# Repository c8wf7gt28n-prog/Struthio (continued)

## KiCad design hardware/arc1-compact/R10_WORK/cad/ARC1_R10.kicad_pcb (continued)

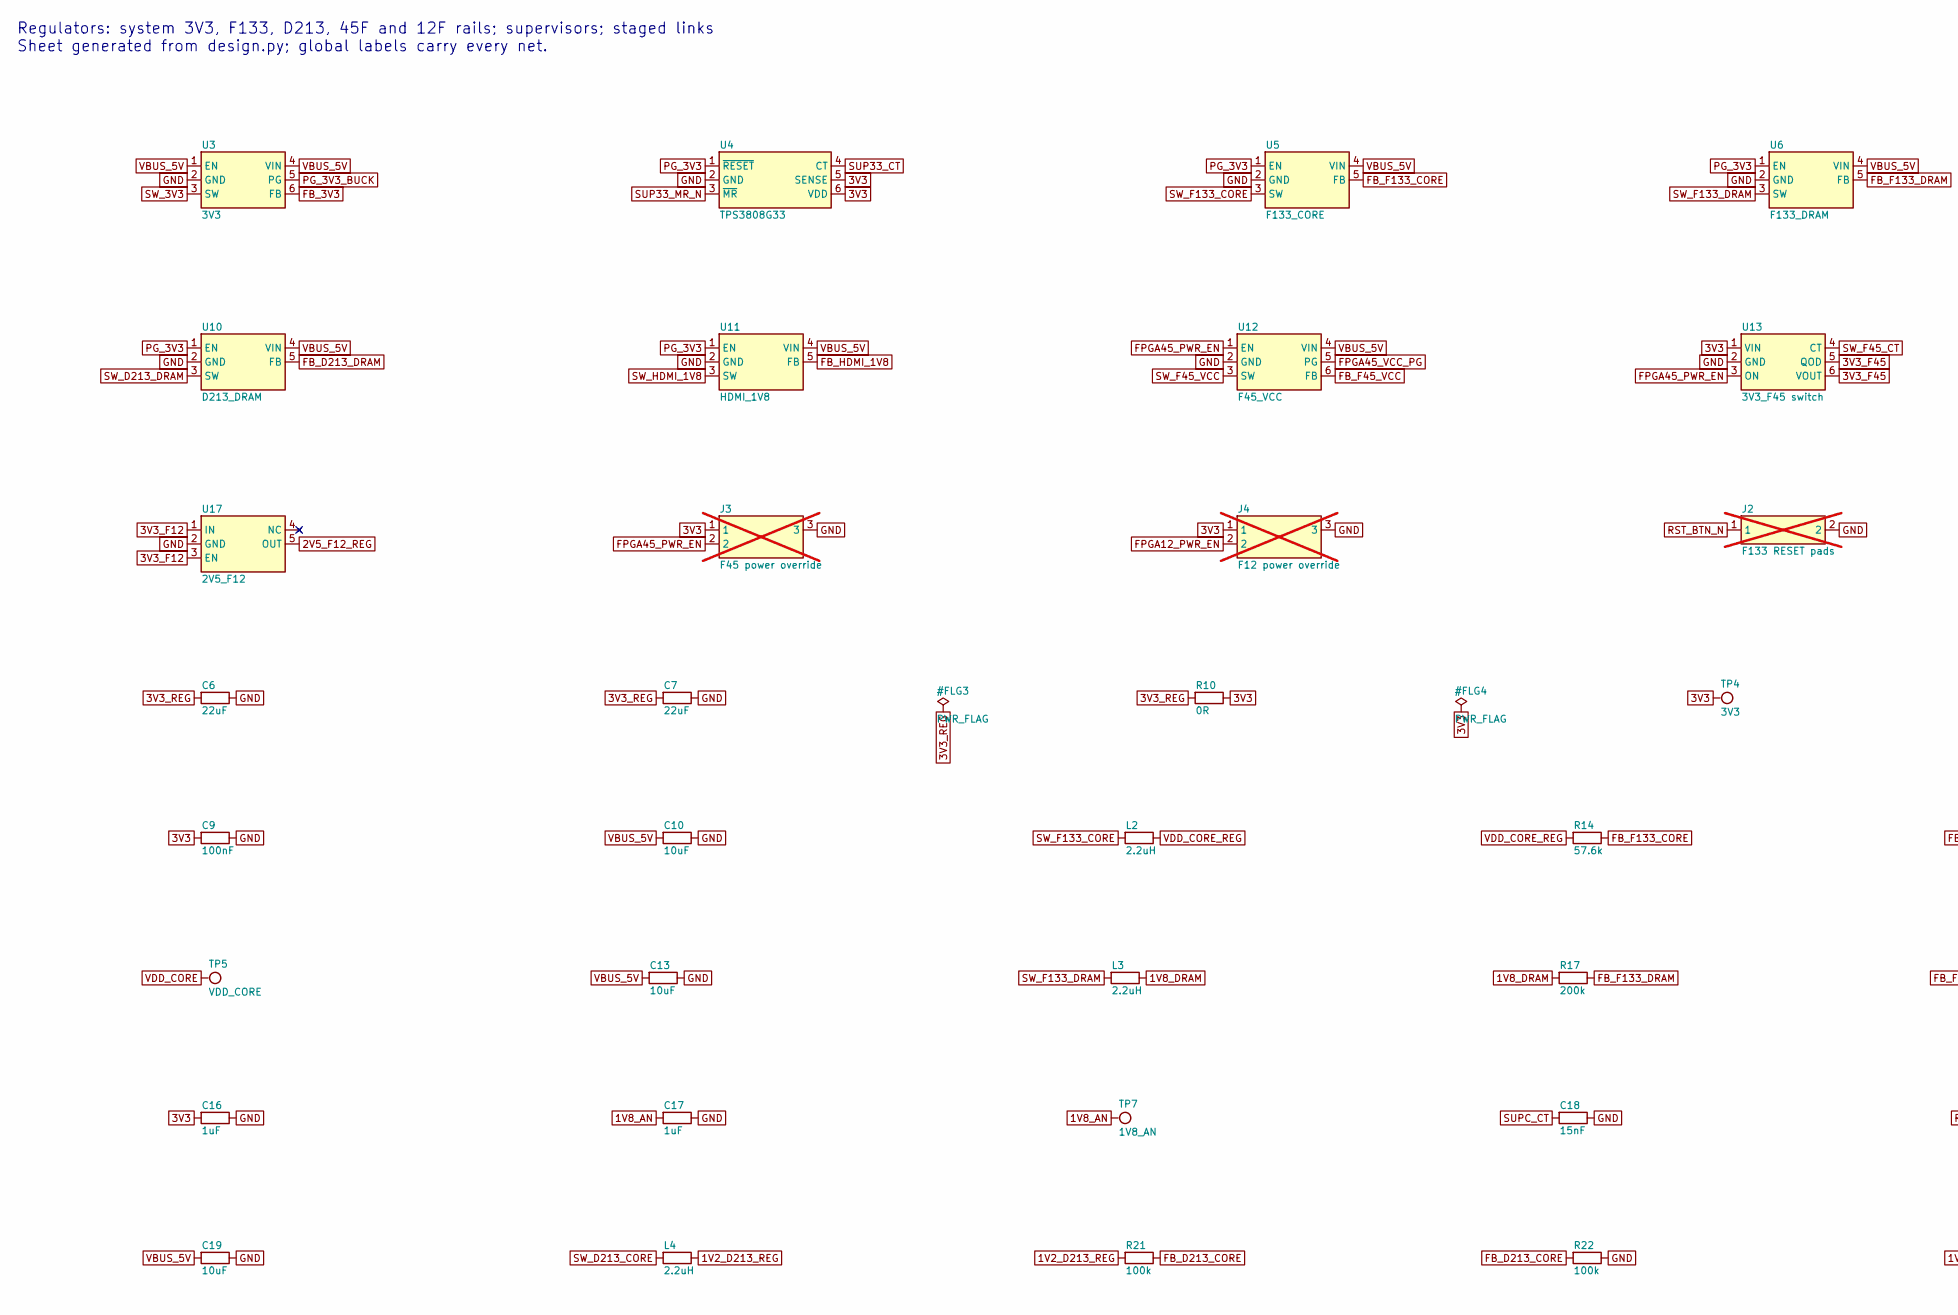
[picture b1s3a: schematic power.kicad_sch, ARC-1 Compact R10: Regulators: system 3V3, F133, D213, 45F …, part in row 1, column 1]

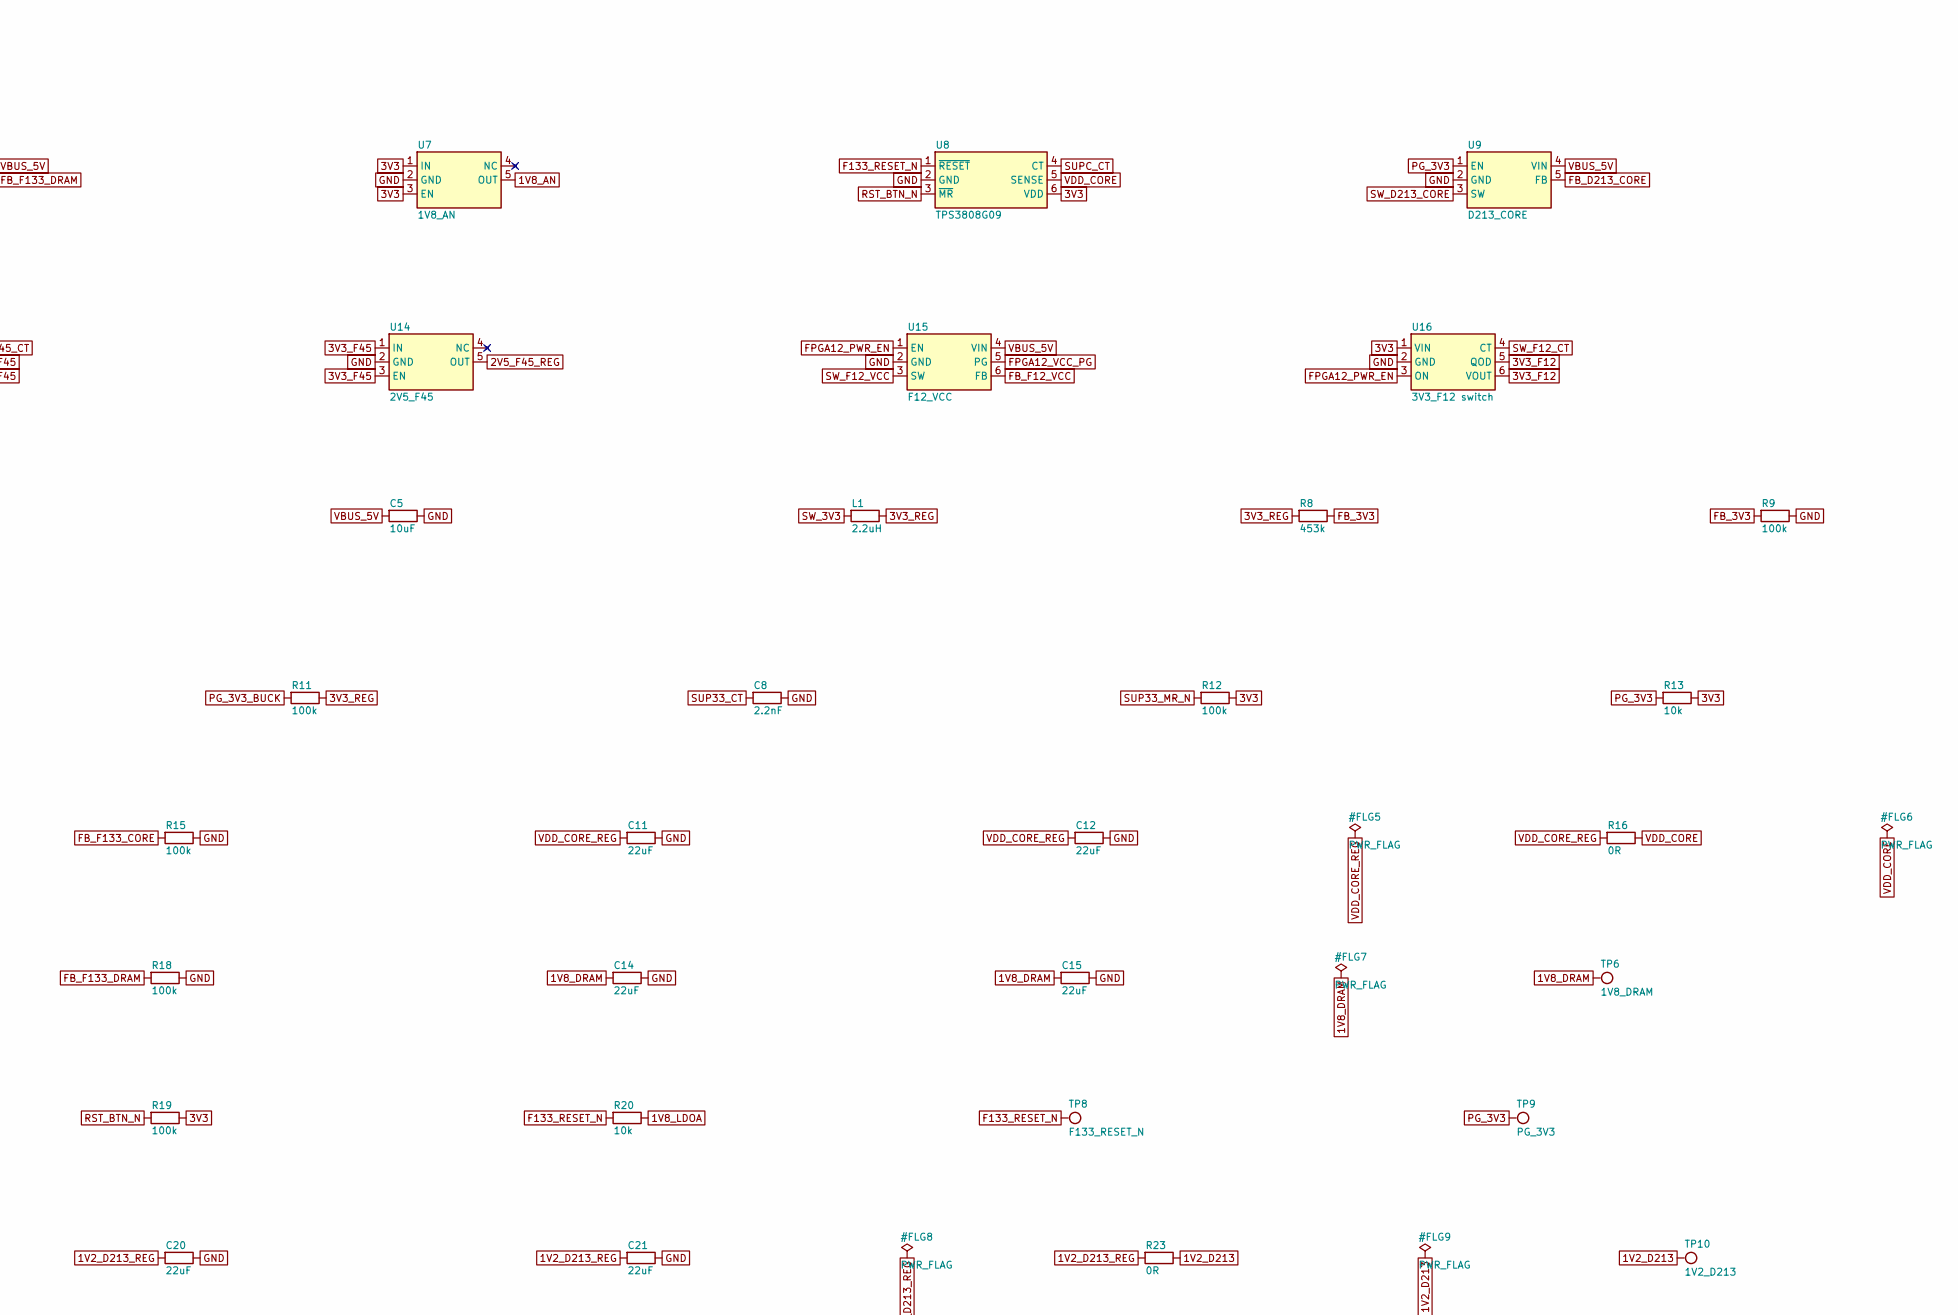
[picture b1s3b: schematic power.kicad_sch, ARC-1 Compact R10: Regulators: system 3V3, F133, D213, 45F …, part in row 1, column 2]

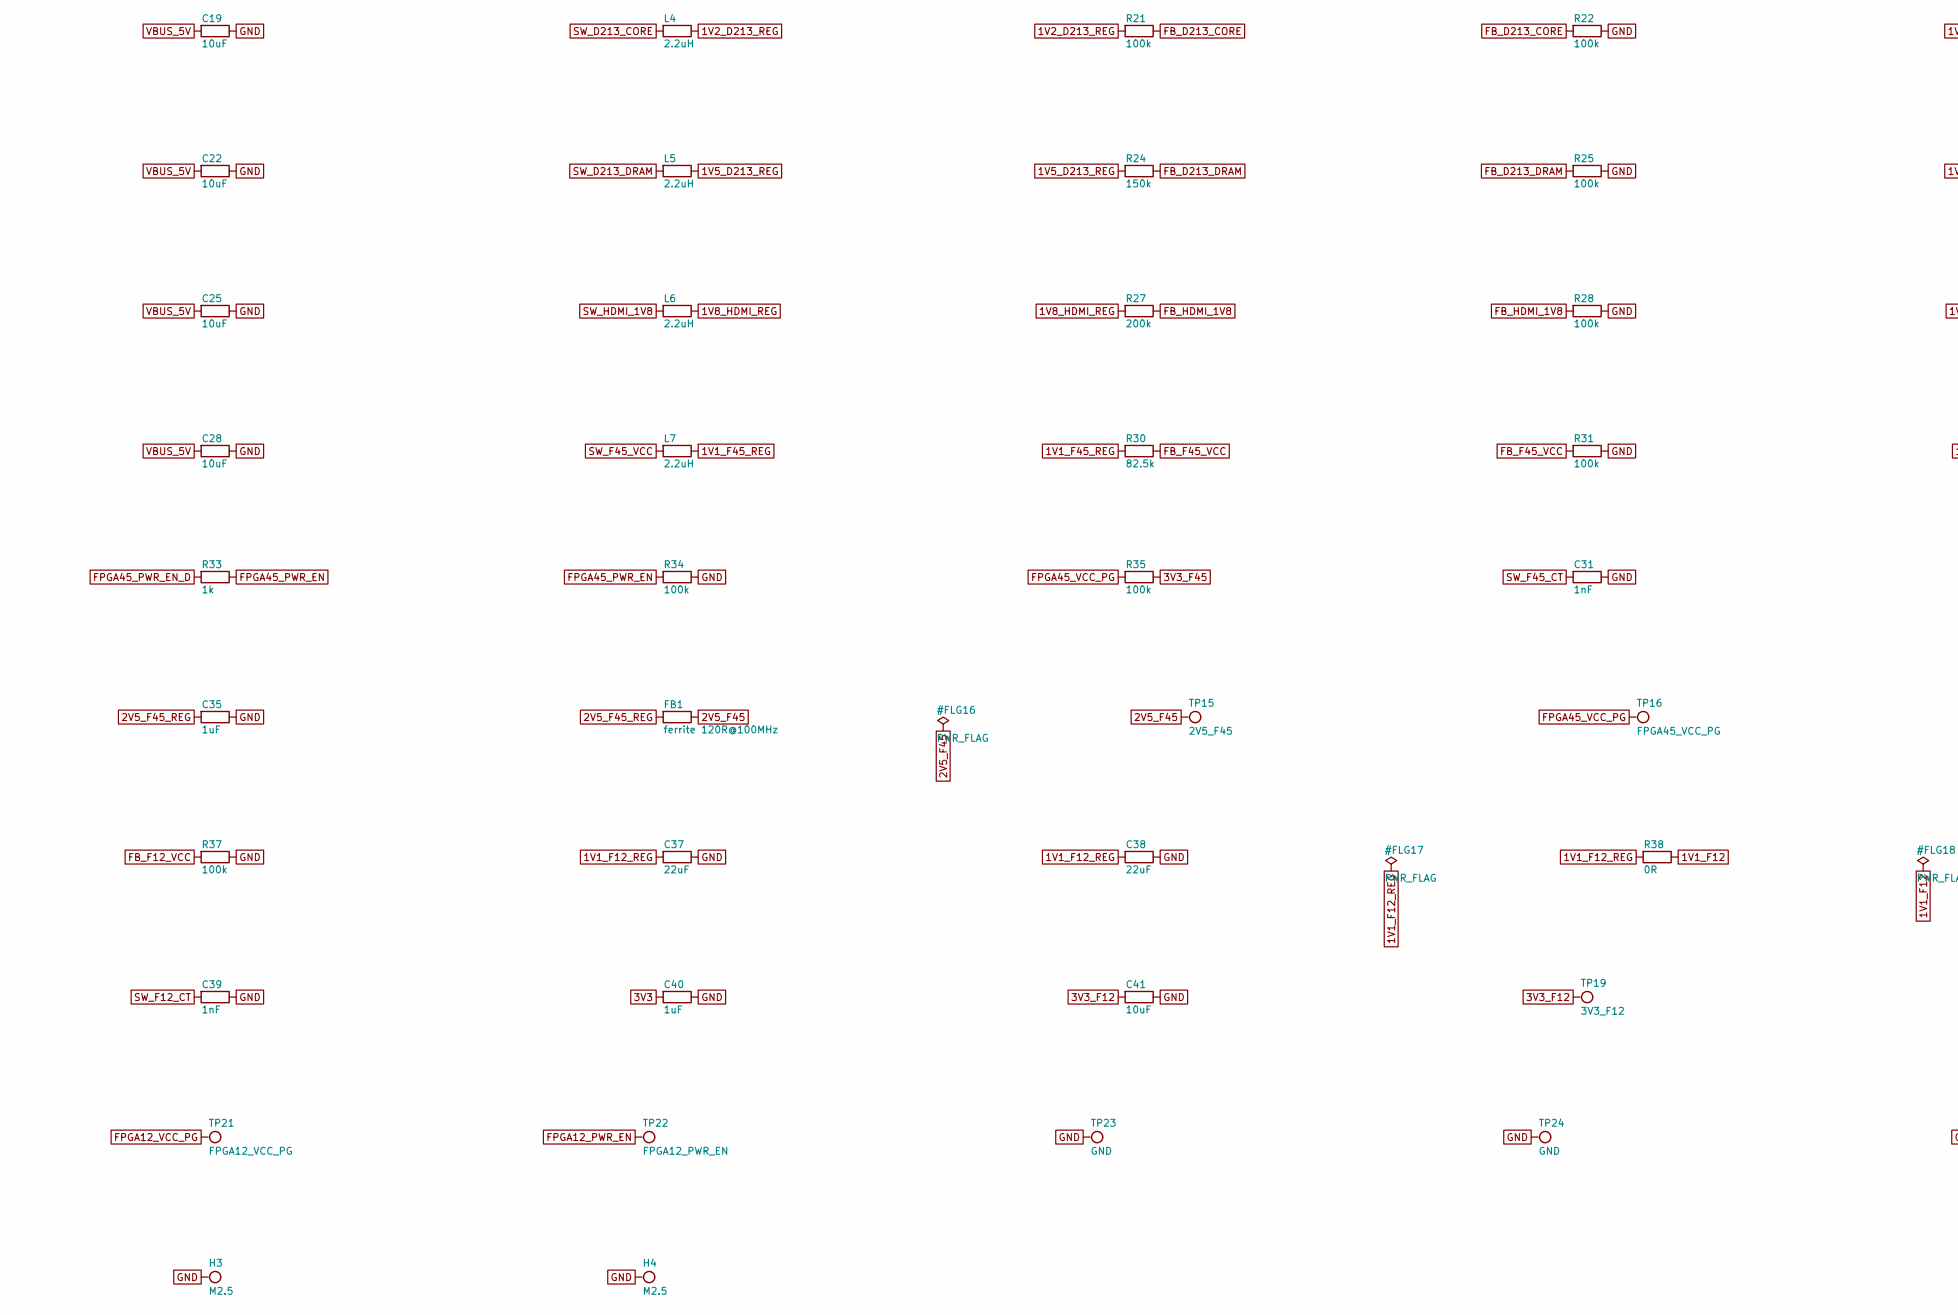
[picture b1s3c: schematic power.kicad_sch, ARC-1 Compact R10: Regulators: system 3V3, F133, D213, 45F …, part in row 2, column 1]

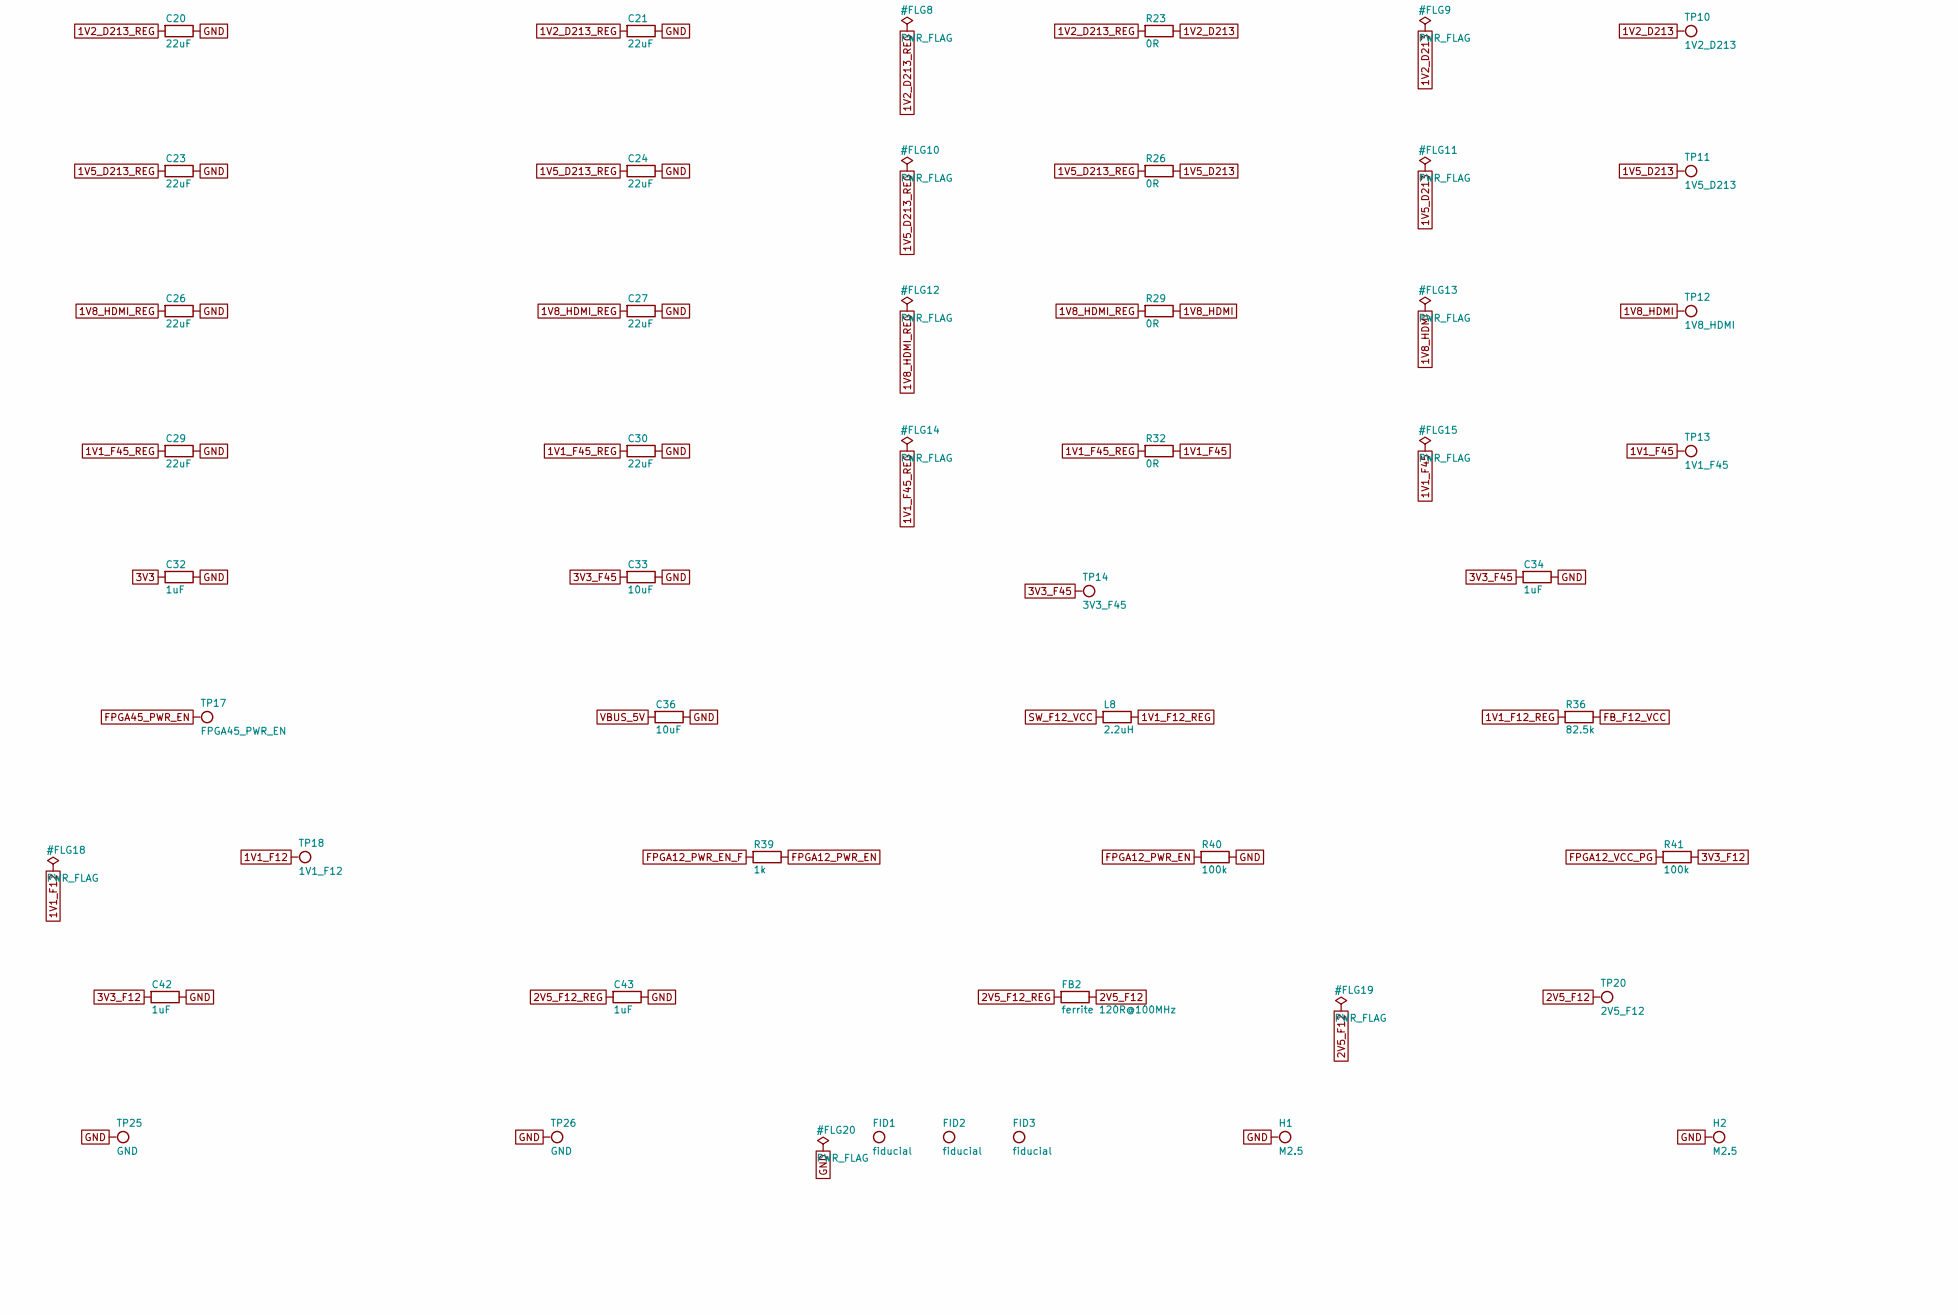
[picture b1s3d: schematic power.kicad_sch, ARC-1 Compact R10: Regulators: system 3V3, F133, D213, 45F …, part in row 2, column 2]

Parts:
C5, C10, C13, C19, C22, C25, C28, C36: 10uF; C_0805_2012Metric; MPN CL21A106KAYNNNE; LCSC C15850
C6, C7, C11, C12, C14, C15, C20, C21, C23, C24, C26, C27, C29, C30, C37, C38: 22uF; C_0805_2012Metric; MPN CL21A226MQQNNNE; LCSC C5674
C8: 2.2nF; C_0402_1005Metric
C9: 100nF; C_0402_1005Metric; MPN CL05B104KO5NNNC; LCSC C1525
C16, C17, C32, C34, C35, C40, C42, C43: 1uF; C_0402_1005Metric; MPN CL05A105KA5NQNC; LCSC C52923
C18: 15nF; C_0402_1005Metric
C31, C39: 1nF; C_0402_1005Metric
C33, C41: 10uF; C_0603_1608Metric; MPN CL10A106KP8NNNC; LCSC C19702
FB1, FB2: ferrite 120R@100MHz; L_0603_1608Metric; MPN BLM18PG121SN1D (CANDIDATE)
FID1, FID2, FID3: fiducial; Fiducial_1mm_Mask2mm
H1, H2, H3, H4: M2.5; MountingHole_2.7mm_M2.5_Pad
J2: F133 RESET pads; TestPoint_2Pads_Pitch2.54mm_Drill0.8mm; MPN internal service pad pair; not fitted
J3: F45 power override; PinHeader_1x03_P2.54mm_Vertical; MPN header 1x3 2.54 (DNP-able); not fitted
J4: F12 power override; PinHeader_1x03_P2.54mm_Vertical; MPN header 1x3 2.54 (DNP-able); not fitted
L1, L2, L3, L4, L5, L6, L7, L8: 2.2uH; SLIM4_FP_L2_ASWPA4035; MPN ASWPA4035S2R2MT; LCSC C340207
R8: 453k; R_0402_1005Metric
R9, R11, R12, R15, R18, R19, R21, R22, R25, R28, R31, R34, R35, R37, R40, R41: 100k; R_0402_1005Metric; MPN 0402WGF1003TCE; LCSC C25741
R10, R16, R23, R26, R29, R32, R38: 0R; R_0603_1608Metric
R13, R20: 10k; R_0402_1005Metric; MPN 0402WGF1002TCE; LCSC C25744
R14: 57.6k; R_0402_1005Metric
R17, R27: 200k; R_0402_1005Metric
R24: 150k; R_0402_1005Metric
R30, R36: 82.5k; R_0402_1005Metric
R33, R39: 1k; R_0402_1005Metric; MPN 0402WGF1001TCE; LCSC C11702
TP4: 3V3; TestPoint_Pad_D1.0mm
TP5: VDD_CORE; TestPoint_Pad_D1.0mm
TP6: 1V8_DRAM; TestPoint_Pad_D1.0mm
TP7: 1V8_AN; TestPoint_Pad_D1.0mm
TP8: F133_RESET_N; TestPoint_Pad_D1.0mm
TP9: PG_3V3; TestPoint_Pad_D1.0mm
TP10: 1V2_D213; TestPoint_Pad_D1.0mm
TP11: 1V5_D213; TestPoint_Pad_D1.0mm
TP12: 1V8_HDMI; TestPoint_Pad_D1.0mm
TP13: 1V1_F45; TestPoint_Pad_D1.0mm
TP14: 3V3_F45; TestPoint_Pad_D1.0mm
TP15: 2V5_F45; TestPoint_Pad_D1.0mm
TP16: FPGA45_VCC_PG; TestPoint_Pad_D1.0mm
TP17: FPGA45_PWR_EN; TestPoint_Pad_D1.0mm
TP18: 1V1_F12; TestPoint_Pad_D1.0mm
TP19: 3V3_F12; TestPoint_Pad_D1.0mm
TP20: 2V5_F12; TestPoint_Pad_D1.0mm
TP21: FPGA12_VCC_PG; TestPoint_Pad_D1.0mm
TP22: FPGA12_PWR_EN; TestPoint_Pad_D1.0mm
TP23, TP24, TP25, TP26: GND; TestPoint_Pad_D1.0mm
U3: 3V3; SOT-23-6; MPN TLV62569PDDCR
U4: TPS3808G33; SOT-23-6; MPN TPS3808G33DBVR
U5: F133_CORE; SOT-23-5; MPN TLV62569DBVR; LCSC C141836
U6: F133_DRAM; SOT-23-5; MPN TLV62569DBVR; LCSC C141836
U7: 1V8_AN; SOT-23-5; MPN TLV75518PDBVR; LCSC C2877863
U8: TPS3808G09; SOT-23-6; MPN TPS3808G09DBVR
U9: D213_CORE; SOT-23-5; MPN TLV62569DBVR; LCSC C141836
U10: D213_DRAM; SOT-23-5; MPN TLV62569DBVR; LCSC C141836
U11: HDMI_1V8; SOT-23-5; MPN TLV62569DBVR; LCSC C141836
U12: F45_VCC; SOT-23-6; MPN TLV62569PDDCR
U13: 3V3_F45 switch; SOT-23-6; MPN TPS22918DBVR
U14: 2V5_F45; SOT-23-5; MPN TLV75525PDBVR
U15: F12_VCC; SOT-23-6; MPN TLV62569PDDCR
U16: 3V3_F12 switch; SOT-23-6; MPN TPS22918DBVR
U17: 2V5_F12; SOT-23-5; MPN TLV75525PDBVR

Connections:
1V1_F12: R38.2, TP18.1; also elsewhere on the board
1V1_F12_REG: C37.1, C38.1, L8.2, R36.1, R38.1
1V1_F45: R32.2, TP13.1; also elsewhere on the board
1V1_F45_REG: C29.1, C30.1, L7.2, R30.1, R32.1
1V2_D213: R23.2, TP10.1; also elsewhere on the board
1V2_D213_REG: C20.1, C21.1, L4.2, R21.1, R23.1
1V5_D213: R26.2, TP11.1; also elsewhere on the board
1V5_D213_REG: C23.1, C24.1, L5.2, R24.1, R26.1
1V8_AN: C17.1, TP7.1, U7.5 (OUT); also elsewhere on the board
1V8_DRAM: C14.1, C15.1, L3.2, R17.1, TP6.1; also elsewhere on the board
1V8_HDMI: R29.2, TP12.1; also elsewhere on the board
1V8_HDMI_REG: C26.1, C27.1, L6.2, R27.1, R29.1
1V8_LDOA: R20.2; also elsewhere on the board
2V5_F12: FB2.2, TP20.1; also elsewhere on the board
2V5_F12_REG: C43.1, FB2.1, U17.5 (OUT)
2V5_F45: FB1.2, TP15.1; also elsewhere on the board
2V5_F45_REG: C35.1, FB1.1, U14.5 (OUT)
3V3: C9.1, C16.1, C32.1, C40.1, J3.1, J4.1, R10.2, R12.2, R13.2, R19.2, TP4.1, U4.5 (SENSE), U4.6 (VDD), U7.1 (IN), U7.3 (EN), U8.6 (VDD), U13.1 (VIN), U16.1 (VIN); also elsewhere on the board
3V3_F12: C41.1, C42.1, R41.2, TP19.1, U16.5 (QOD), U16.6 (VOUT), U17.1 (IN), U17.3 (EN); also elsewhere on the board
3V3_F45: C33.1, C34.1, R35.2, TP14.1, U13.5 (QOD), U13.6 (VOUT), U14.1 (IN), U14.3 (EN); also elsewhere on the board
3V3_REG: C6.1, C7.1, L1.2, R8.1, R10.1, R11.2
F133_RESET_N: R20.1, TP8.1, U8.1 (~RESET); also elsewhere on the board
FB_3V3: R8.2, R9.1, U3.6 (FB)
FB_D213_CORE: R21.2, R22.1, U9.5 (FB)
FB_D213_DRAM: R24.2, R25.1, U10.5 (FB)
FB_F12_VCC: R36.2, R37.1, U15.6 (FB)
FB_F45_VCC: R30.2, R31.1, U12.6 (FB)
FB_F133_CORE: R14.2, R15.1, U5.5 (FB)
FB_F133_DRAM: R17.2, R18.1, U6.5 (FB)
FB_HDMI_1V8: R27.2, R28.1, U11.5 (FB)
FPGA12_PWR_EN: J4.2, R39.2, R40.1, TP22.1, U15.1 (EN), U16.3 (ON)
FPGA12_PWR_EN_F: R39.1; also elsewhere on the board
FPGA12_VCC_PG: R41.1, TP21.1, U15.5 (PG); also elsewhere on the board
FPGA45_PWR_EN: J3.2, R33.2, R34.1, TP17.1, U12.1 (EN), U13.3 (ON)
FPGA45_PWR_EN_D: R33.1; also elsewhere on the board
FPGA45_VCC_PG: R35.1, TP16.1, U12.5 (PG); also elsewhere on the board
GND: C5.2, C6.2, C7.2, C8.2, C9.2, C10.2, C11.2, C12.2, C13.2, C14.2, C15.2, C16.2, C17.2, C18.2, C19.2, C20.2, C21.2, C22.2, C23.2, C24.2, C25.2, C26.2, C27.2, C28.2, C29.2, C30.2, C31.2, C32.2, C33.2, C34.2, C35.2, C36.2, C37.2, C38.2, C39.2, C40.2, C41.2, C42.2, C43.2, H1.1, H2.1, H3.1, H4.1, J2.2, J3.3, J4.3, R9.2, R15.2, R18.2, R22.2, R25.2, R28.2, R31.2, R34.2, R37.2, R40.2, TP23.1, TP24.1, TP25.1, TP26.1, U3.2 (GND), U4.2 (GND), U5.2 (GND), U6.2 (GND), U7.2 (GND), U8.2 (GND), U9.2 (GND), U10.2 (GND), U11.2 (GND), U12.2 (GND), U13.2 (GND), U14.2 (GND), U15.2 (GND), U16.2 (GND), U17.2 (GND); also elsewhere on the board
PG_3V3: R13.1, TP9.1, U4.1 (~RESET), U5.1 (EN), U6.1 (EN), U9.1 (EN), U10.1 (EN), U11.1 (EN)
PG_3V3_BUCK: R11.1, U3.5 (PG)
RST_BTN_N: J2.1, R19.1, U8.3 (~MR)
SUP33_CT: C8.1, U4.4 (CT)
SUP33_MR_N: R12.1, U4.3 (~MR)
SUPC_CT: C18.1, U8.4 (CT)
SW_3V3: L1.1, U3.3 (SW)
SW_D213_CORE: L4.1, U9.3 (SW)
SW_D213_DRAM: L5.1, U10.3 (SW)
SW_F12_CT: C39.1, U16.4 (CT)
SW_F12_VCC: L8.1, U15.3 (SW)
SW_F45_CT: C31.1, U13.4 (CT)
SW_F45_VCC: L7.1, U12.3 (SW)
SW_F133_CORE: L2.1, U5.3 (SW)
SW_F133_DRAM: L3.1, U6.3 (SW)
SW_HDMI_1V8: L6.1, U11.3 (SW)
VBUS_5V: C5.1, C10.1, C13.1, C19.1, C22.1, C25.1, C28.1, C36.1, U3.1 (EN), U3.4 (VIN), U5.4 (VIN), U6.4 (VIN), U9.4 (VIN), U10.4 (VIN), U11.4 (VIN), U12.4 (VIN), U15.4 (VIN); also elsewhere on the board
VDD_CORE: R16.2, TP5.1, U8.5 (SENSE); also elsewhere on the board
VDD_CORE_REG: C11.1, C12.1, L2.2, R14.1, R16.1

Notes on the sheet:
Regulators: system 3V3, F133, D213, 45F and 12F rails; supervisors; staged links Sheet generated from design.py; global labels carry every net.
